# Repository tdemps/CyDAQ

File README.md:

# master_EE_224
This is the repository for the Iowa State University teaching lab's CyDAQ hardware. The CyDAQ is a data acquisition system designed around the Zybo Z7 FPGA. It features analog inputs to a filter block feature 7 adjustable filters, power breakout, and Zybo PMOD breakouts. 

## Filters:
The board features the following 7 filters:
    - 60 Hz Notch 
    - 1st Order High Pass
    - 1st Order Low Pass
    - 2nd Order Bandpass
    - 6th Order How Pass
    - 6th Order Low pass
    - 6th Order Bandpass

Each of these filters can be selected to process any of the analog inputs, and their outputs are sent to the XADC on the Zybo and the Vout breakout header. 

## Power
The board has three user accessible power rails: 1.8V, 3.3V, and 5.0V. Each rail can source up to 1A. 

## Digital Communication Protocols
The board breaks out I2C and UART busses accessible through the Zybo.

## Firmware
See README in /src/firmware details

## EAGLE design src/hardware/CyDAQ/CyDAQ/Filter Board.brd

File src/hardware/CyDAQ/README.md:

# CyDAQ 2.0

Build of CyDAQ 2.0 with ZYBO Z7

TODO:

Design power block and add sheet

Import filter design

Establish I/O connectors

Design ADC front end

Design filter board input mux

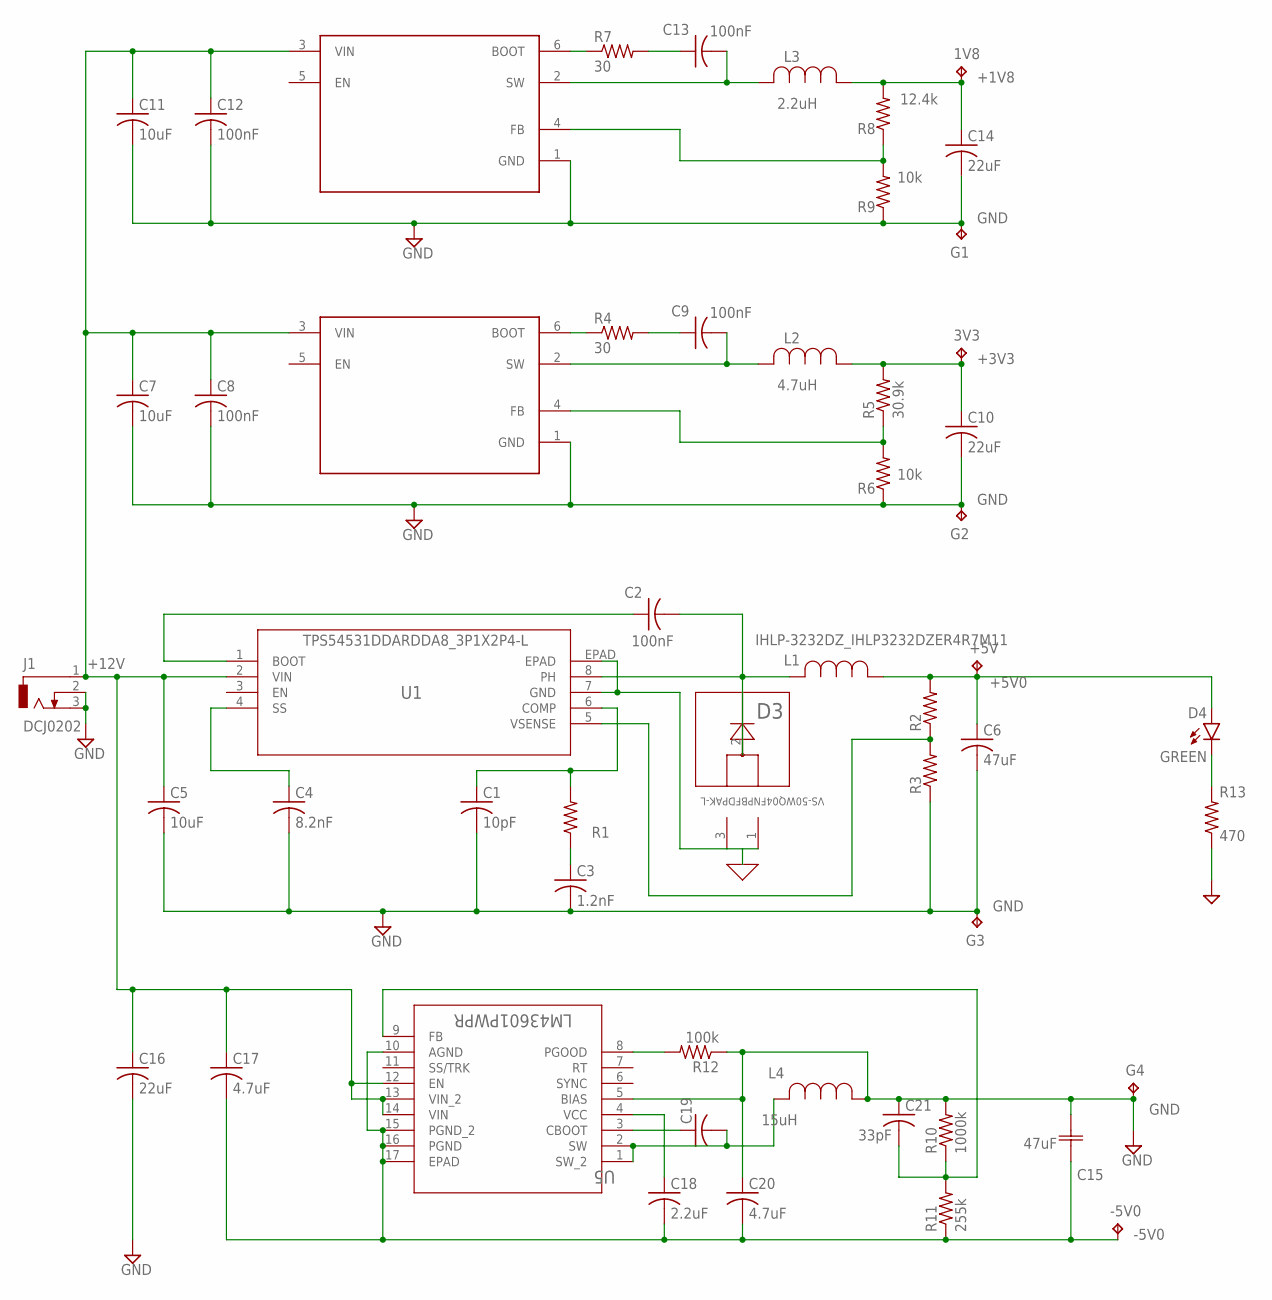
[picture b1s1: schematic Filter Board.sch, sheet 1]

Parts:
1V8, 3V3: TPPAD1-13; P1-13
+5V: TPPAD1-13; P1-13
-5V0: TPPAD1-13; P1-13
C1: 10pF; C0805
C2, C8, C9, C12, C13: 100nF; C0805
C3: 1.2nF; C0805
C4: 8.2nF; C1206
C5: 10uF; C1210
C6: 47uF; C1210
C7, C11: 10uF; C0805
C10, C14: 22uF; C0805
C15: 47uF; CGA9N3X7R1_CAP_5750
C16: 22uF; C1210
C17, C20: 4.7uF; C0805
C18: 2.2uF; C0805
C19: C-USC0805; C0805
C21: 33pF; C0805
D3: VS-50WQ04FNPBFDPAK-L; DPAK-L
D4: GREEN; LED-1206
G1, G2, G3, G4: TPPAD1-13; P1-13
J1: DCJ0202
L1: IHLP-3232DZ_IHLP3232DZER4R7M11; IHLP-3232DZ_IND_IHLP-3232DZ
L2: 4.7uH; IND_5022
L3: 2.2uH; IND_NLCV32TR; MANUFACTURER_PART_NUMBER NLCV32T-2R2M-PFR
L4: 15uH; IFSC-1515A_IND_IFSC_1515AH
R1, R2, R3: R-US_R0805; R0805
R4, R7: 30; R0805
R5: 30.9k; R0805
R6, R9: 10k; R0805
R8: 12.4k; R0805
R10: 1000k; R0805
R11: 255k; R0805
R12: 100k; R0805
R13: 470; R0805
U1: TPS54531DDARDDA8_3P1X2P4-L; DDA8_3P1X2P4-L
U3, U4: TPS56339; TSOT23-6_DDC
U5: LM43601PWPR; PWP16

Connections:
+1V8: 1V8.TP, C14.1, L3.1, R8.2; also elsewhere on the board
+3V3: 3V3.TP, C10.1, L2.1, R5.2; also elsewhere on the board
+5V0: +5V.TP, C6.1, D4.A, L1.1, R2.2; also elsewhere on the board
+12V: C5.1, C7.1, C8.1, C11.1, C12.1, C16.1, C17.1, J1.1, U1.2 (VIN), U3.3 (VIN), U4.3 (VIN), U5.12 (EN), U5.13 (VIN_2), U5.14 (VIN); also elsewhere on the board
-5V0: -5V0.TP, C15.2, C17.2, C18.2, C20.2, R11.1, U5.10 (AGND), U5.15 (PGND_2), U5.16 (PGND), U5.17 (EPAD); also elsewhere on the board
BOOT: C19.1, U5.3 (CBOOT)
FB: C21.2, R10.1, R11.2, U5.9 (FB)
GND: C1.2, C3.2, C4.2, C5.2, C6.2, C7.2, C8.2, C10.2, C11.2, C12.2, C14.2, C15.1, C16.2, C20.1, C21.1, D3.1, D3.3, G1.TP, G2.TP, G3.TP, G4.TP, J1.2, J1.3, L4.1, R3.1, R6.1, R9.1, R10.2, R12.1, R13.1, U1.7 (GND), U1.EPAD, U3.1 (GND), U4.1 (GND), U5.5 (BIAS); also elsewhere on the board
unnamed: C3.1, R1.1
unnamed: R2.1, R3.2, U1.5 (VSENSE)
unnamed: C2.1, U1.1 (BOOT)
unnamed: C2.2, D3.2, L1.2, U1.8 (PH)
unnamed: C4.1, U1.4 (SS)
unnamed: C1.1, R1.2, U1.6 (COMP)
unnamed: R4.1, U3.6 (BOOT)
unnamed: C9.1, R4.2
unnamed: C9.2, L2.2, U3.2 (SW)
unnamed: R7.1, U4.6 (BOOT)
unnamed: R5.1, R6.2, U3.4 (FB)
unnamed: C13.1, R7.2
unnamed: C13.2, L3.2, U4.2 (SW)
unnamed: R8.1, R9.2, U4.4 (FB)
unnamed: C18.1, U5.4 (VCC)
unnamed: D4.C, R13.2
PGOOD: R12.2, U5.8 (PGOOD)
SW: C19.2, L4.2, U5.1 (SW_2), U5.2 (SW)

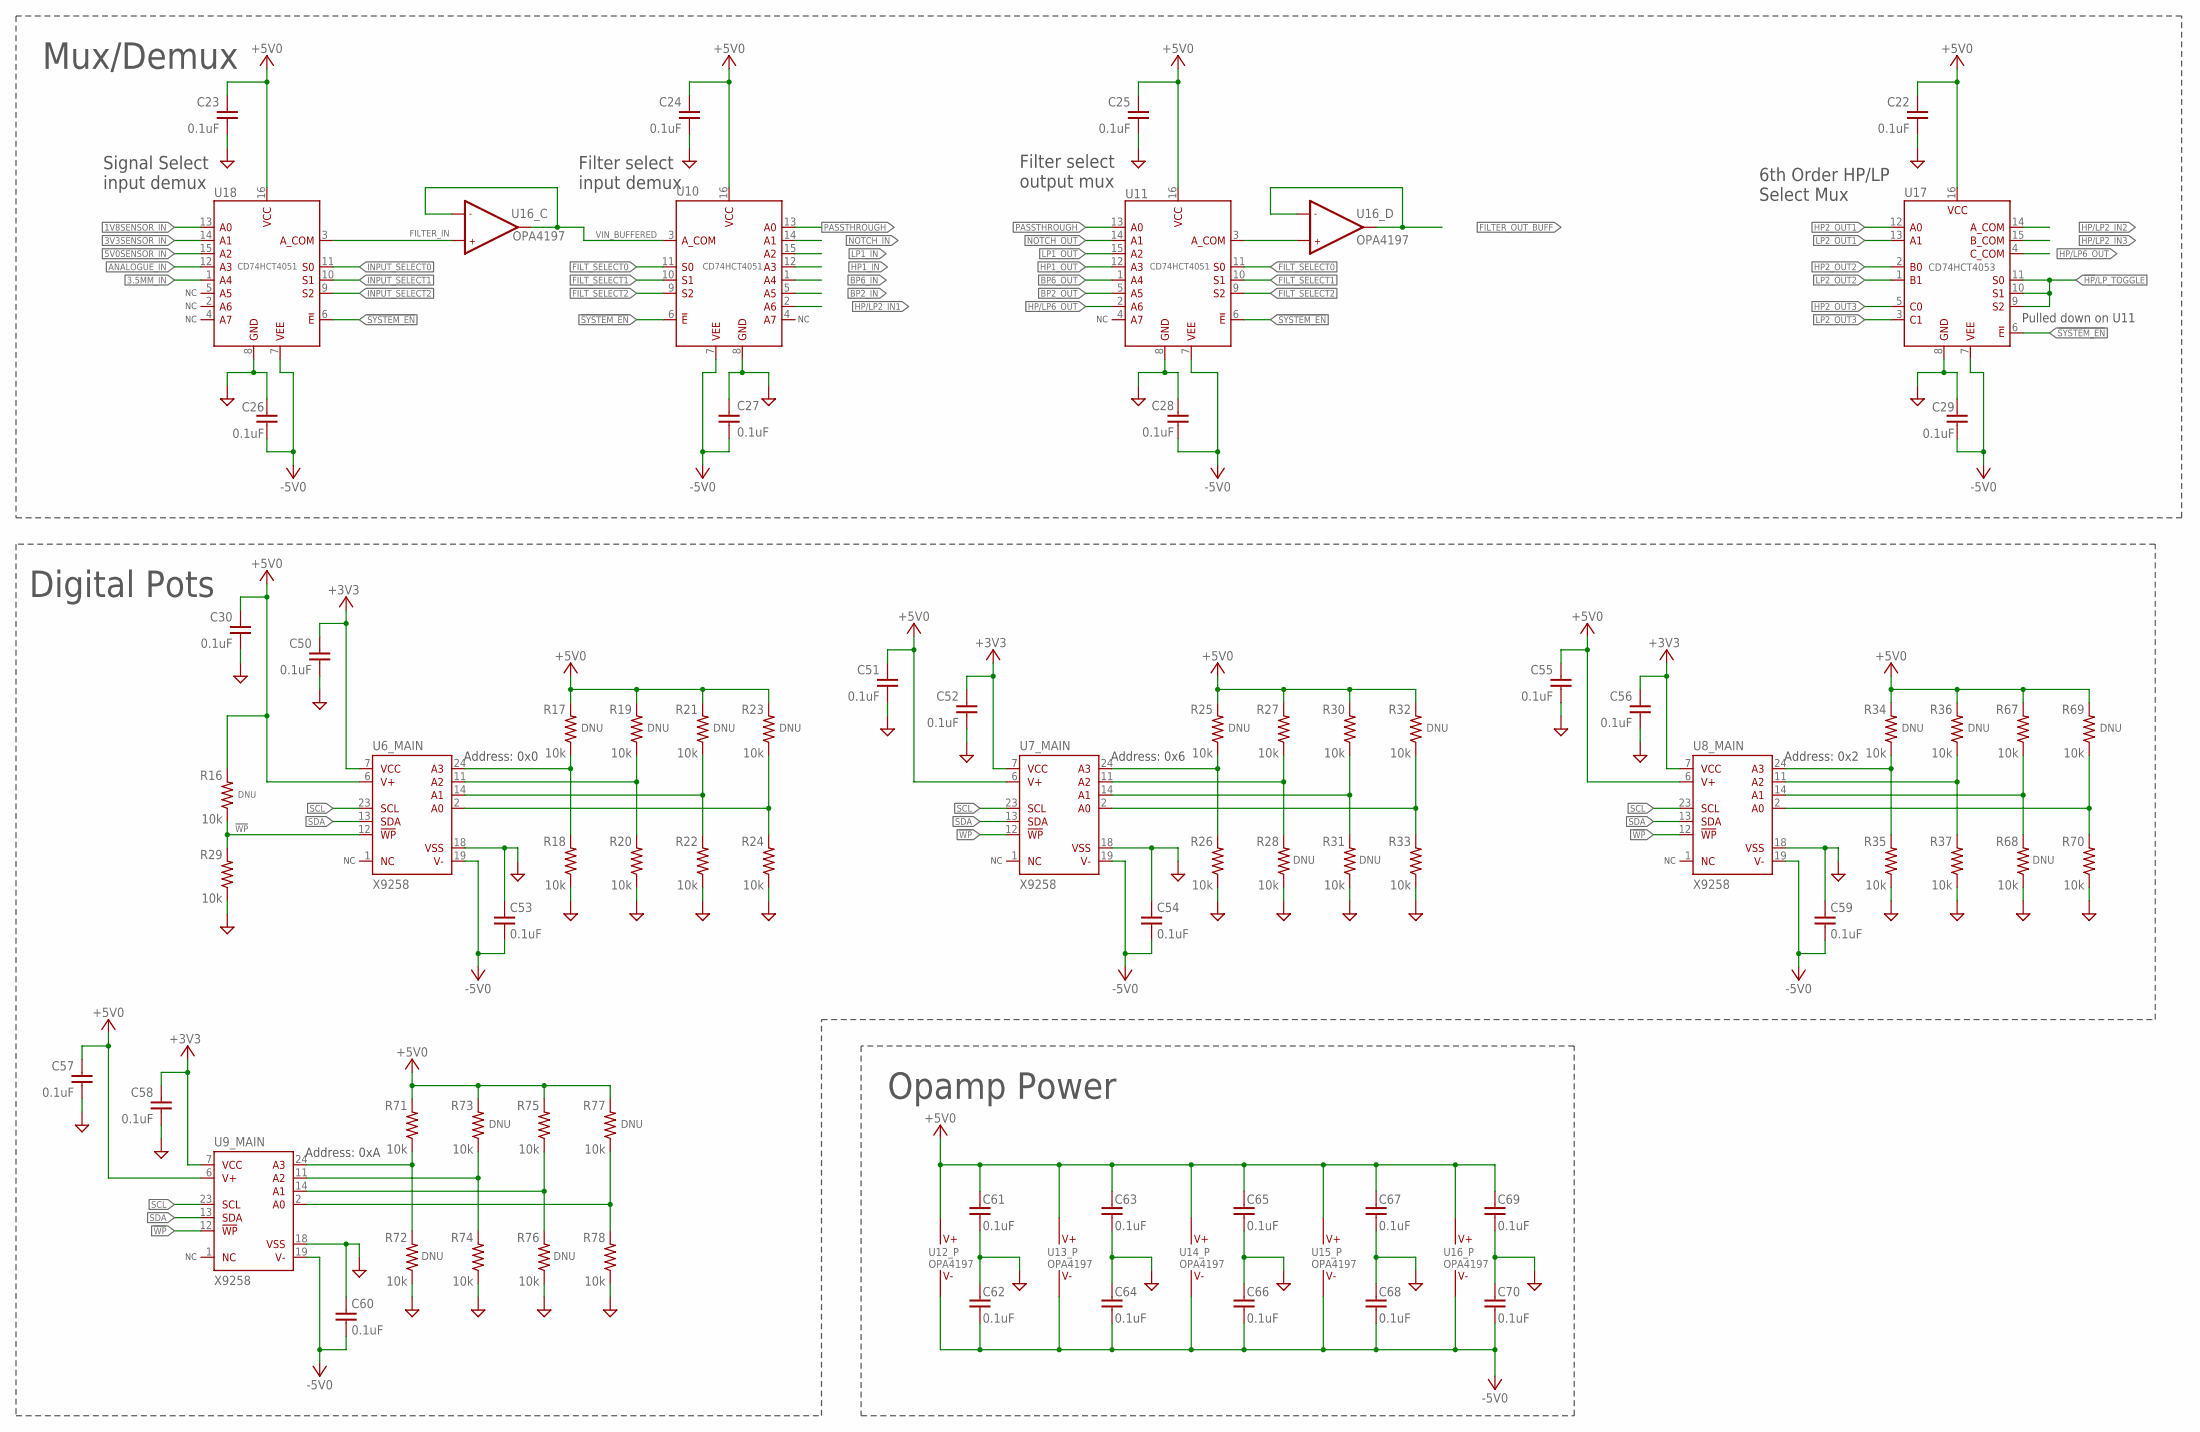
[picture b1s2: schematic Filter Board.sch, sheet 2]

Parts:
C22, C23, C24, C25, C26, C27, C28, C29, C30, C50, C51, C52, C53, C54, C55, C56, C57, C58, C59, C60, C61, C62, C63, C64, C65, C66, C67, C68, C69, C70: 0.1uF; 0805_H0.75
R16, R17, R18, R19, R20, R21, R22, R23, R24, R25, R26, R27, R28, R29, R30, R31, R32, R33, R34, R35, R36, R37, R67, R68, R69, R70, R71, R72, R73, R74, R75, R76, R77, R78: 10k; 0805
U6, U7, U8, U9: X9258; SOIC127P1030X250-25T200X300
U10, U11, U18: CD74HCT4051; SOIC127P600X144-16
U12, U13, U14, U15, U16: OPA4197; SOIC127P600X144-14
U17: CD74HCT4053; SOIC127P600X144-16

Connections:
1V8SENSOR_IN: U18.13 (A0); also elsewhere on the board
3.5MM_IN: U18.1 (A4); also elsewhere on the board
3V3SENSOR_IN: U18.14 (A1); also elsewhere on the board
5V0SENSOR_IN: U18.15 (A2); also elsewhere on the board
!HP!/LP_TOGGLE: U17.9 (S2), U17.10 (S1), U17.11 (S0); also elsewhere on the board
!SYSTEM_EN: U10.6 (!E), U11.6 (!E), U17.6 (!E), U18.6 (!E); also elsewhere on the board
!WP: R16.1, R29.2, U6.12 (!WP), U7.12 (!WP), U8.12 (!WP), U9.12 (!WP)
+3V3: C50.1, C52.1, C56.1, C58.1, U6.7 (VCC), U7.7 (VCC), U8.7 (VCC), U9.7 (VCC); also elsewhere on the board
+5V0: C22.1, C23.1, C24.1, C25.1, C30.1, C51.1, C55.1, C57.1, C61.1, C63.1, C65.1, C67.1, C69.1, R16.2, R17.2, R19.2, R21.2, R23.2, R25.2, R27.2, R30.2, R32.2, R34.2, R36.2, R67.2, R69.2, R71.2, R73.2, R75.2, R77.2, U6.6 (V+), U7.6 (V+), U8.6 (V+), U9.6 (V+), U10.16 (VCC), U11.16 (VCC), U12.4 (V+), U13.4 (V+), U14.4 (V+), U15.4 (V+), U16.4 (V+), U17.16 (VCC), U18.16 (VCC); also elsewhere on the board
-5V0: C26.2, C27.1, C28.2, C29.2, C53.2, C54.2, C59.2, C60.2, C62.2, C64.2, C66.2, C68.2, C70.2, U6.19 (V-), U7.19 (V-), U8.19 (V-), U9.19 (V-), U10.7 (VEE), U11.7 (VEE), U12.11 (V-), U13.11 (V-), U14.11 (V-), U15.11 (V-), U16.11 (V-), U17.7 (VEE), U18.7 (VEE); also elsewhere on the board
ANALOGUE_IN: U18.12 (A3); also elsewhere on the board
BP2_IN: U10.5 (A5); also elsewhere on the board
BP2_OUT: U11.5 (A5); also elsewhere on the board
BP6_IN: U10.1 (A4); also elsewhere on the board
BP6_OUT: U11.1 (A4); also elsewhere on the board
FILTER_IN: U16.10 (+IN), U18.3 (A_COM)
FILTER_OUT_BUFF: U16.13 (-IN), U16.14 (OUT); also elsewhere on the board
FILT_SELECT0: U10.11 (S0), U11.11 (S0); also elsewhere on the board
FILT_SELECT1: U10.10 (S1), U11.10 (S1); also elsewhere on the board
FILT_SELECT2: U10.9 (S2), U11.9 (S2); also elsewhere on the board
GND: C22.2, C23.2, C24.2, C25.2, C26.1, C27.2, C28.1, C29.1, C30.2, C50.2, C51.2, C52.2, C53.1, C54.1, C55.2, C56.2, C57.2, C58.2, C59.1, C60.1, C61.2, C62.1, C63.2, C64.1, C65.2, C66.1, C67.2, C68.1, C69.2, C70.1, R18.1, R20.1, R22.1, R24.1, R26.1, R28.1, R29.1, R31.1, R33.1, R35.1, R37.1, R68.1, R70.1, R72.1, R74.1, R76.1, R78.1, U6.18 (VSS), U7.18 (VSS), U8.18 (VSS), U9.18 (VSS), U10.8 (GND), U11.8 (GND), U17.8 (GND), U18.8 (GND); also elsewhere on the board
HP1_IN: U10.12 (A3); also elsewhere on the board
HP1_OUT: U11.12 (A3); also elsewhere on the board
HP2_OUT1: U17.12 (A0); also elsewhere on the board
HP2_OUT2: U17.2 (B0); also elsewhere on the board
HP2_OUT3: U17.5 (C0); also elsewhere on the board
HP/LP2_IN1: U10.2 (A6); also elsewhere on the board
HP/LP2_IN2: U17.14 (A_COM); also elsewhere on the board
HP/LP2_IN3: U17.15 (B_COM); also elsewhere on the board
HP/LP6_OUT: U11.2 (A6), U17.4 (C_COM)
INPUT_SELECT0: U18.11 (S0); also elsewhere on the board
INPUT_SELECT1: U18.10 (S1); also elsewhere on the board
INPUT_SELECT2: U18.9 (S2); also elsewhere on the board
LP1_IN: U10.15 (A2); also elsewhere on the board
LP1_OUT: U11.15 (A2); also elsewhere on the board
LP2_OUT1: U17.13 (A1); also elsewhere on the board
LP2_OUT2: U17.1 (B1); also elsewhere on the board
LP2_OUT3: U17.3 (C1); also elsewhere on the board
unnamed: R17.1, R18.2, U6.24 (A3)
unnamed: R19.1, R20.2, U6.11 (A2)
unnamed: R21.1, R22.2, U6.14 (A1)
unnamed: U11.3 (A_COM), U16.12 (+IN)
unnamed: R23.1, R24.2, U6.2 (A0)
unnamed: R25.1, R26.2, U7.24 (A3)
unnamed: R27.1, R28.2, U7.11 (A2)
unnamed: R30.1, R31.2, U7.14 (A1)
unnamed: R32.1, R33.2, U7.2 (A0)
unnamed: R34.1, R35.2, U8.24 (A3)
unnamed: R36.1, R37.2, U8.11 (A2)
unnamed: R67.1, R68.2, U8.14 (A1)
unnamed: R69.1, R70.2, U8.2 (A0)
unnamed: R71.1, R72.2, U9.24 (A3)
unnamed: R73.1, R74.2, U9.11 (A2)
unnamed: R75.1, R76.2, U9.14 (A1)
unnamed: R77.1, R78.2, U9.2 (A0)
NOTCH_IN: U10.14 (A1); also elsewhere on the board
NOTCH_OUT: U11.14 (A1); also elsewhere on the board
PASSTHROUGH: U10.13 (A0), U11.13 (A0)
SCL: U6.23 (SCL), U7.23 (SCL), U8.23 (SCL), U9.23 (SCL); also elsewhere on the board
SDA: U6.13 (SDA), U7.13 (SDA), U8.13 (SDA), U9.13 (SDA); also elsewhere on the board
VIN_BUFFERED: U10.3 (A_COM), U16.8 (OUT), U16.9 (-IN)

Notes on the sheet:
Address: 0x0
Address: 0x6
Address: 0x2
Address: 0xA
Opamp Power
Digital Pots
Mux/Demux
6th Order HP/LP Select Mux
Filter select input demux
Filter select output mux
Pulled down on U11
Signal Select input demux

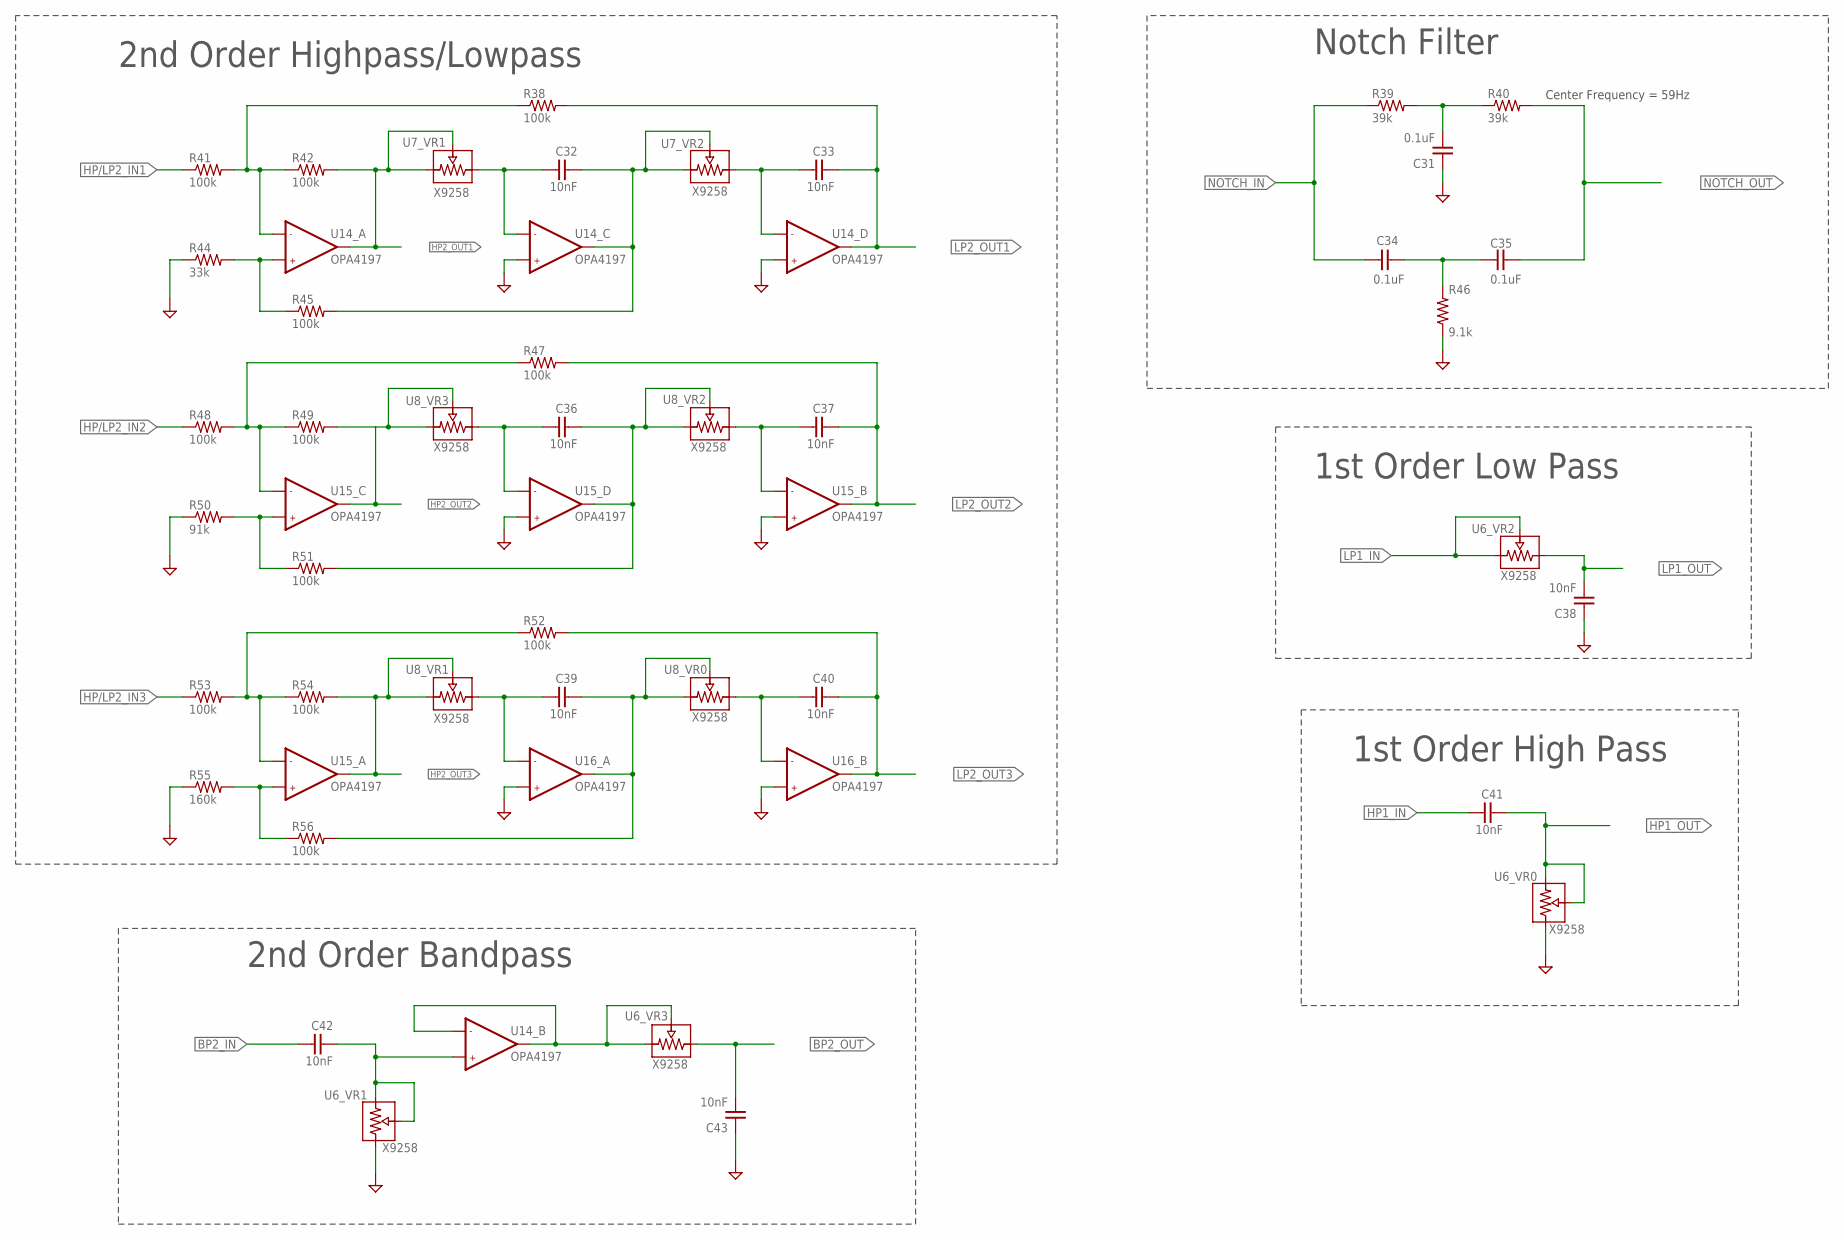
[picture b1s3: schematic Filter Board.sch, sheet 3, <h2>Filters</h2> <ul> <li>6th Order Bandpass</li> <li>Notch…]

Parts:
C31, C34, C35: 0.1uF; 0805_H0.75
C32, C33, C36, C37, C38, C39, C40, C41, C42, C43: 10nF; 0805_H0.75
R38, R41, R42, R45, R47, R48, R49, R51, R52, R53, R54, R56: 100k; 0805
R39, R40: 39k; 0805
R44: 33k; 0805
R46: 9.1k; 0805
R50: 91k; 0805
R55: 160k; 0805
U6, U7, U8: X9258; SOIC127P1030X250-25T200X300
U14, U15, U16: OPA4197; SOIC127P600X144-14

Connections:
BP2_IN: C42.1; also elsewhere on the board
BP2_OUT: C43.2, U6.5 (L); also elsewhere on the board
GND: C31.1, C38.1, C43.1, R44.1, R46.1, R50.1, R55.1, U6.8 (L), U6.15 (L), U14.10 (+IN), U14.12 (+IN), U15.5 (+IN), U15.12 (+IN), U16.3 (+IN), U16.5 (+IN); also elsewhere on the board
HP1_IN: C41.1; also elsewhere on the board
HP1_OUT: C41.2, U6.9 (H), U6.10 (W); also elsewhere on the board
HP2_OUT1: R42.2, U7.16 (H), U7.17 (W), U14.1 (OUT); also elsewhere on the board
HP2_OUT2: R49.2, U8.3 (W), U8.4 (H), U15.8 (OUT); also elsewhere on the board
HP2_OUT3: R54.2, U8.16 (H), U8.17 (W), U15.1 (OUT); also elsewhere on the board
HP/LP2_IN1: R41.1; also elsewhere on the board
HP/LP2_IN2: R48.1; also elsewhere on the board
HP/LP2_IN3: R53.1; also elsewhere on the board
LP1_IN: U6.20 (W), U6.21 (H); also elsewhere on the board
LP1_OUT: C38.2, U6.22 (L); also elsewhere on the board
LP2_OUT1: C33.2, R38.2, U14.14 (OUT); also elsewhere on the board
LP2_OUT2: C37.2, R47.2, U15.7 (OUT); also elsewhere on the board
LP2_OUT3: C40.2, R52.2, U16.7 (OUT); also elsewhere on the board
unnamed: C31.2, R39.2, R40.1
unnamed: C34.2, C35.1, R46.2
unnamed: C42.2, U6.16 (H), U6.17 (W), U14.5 (+IN)
unnamed: U6.3 (W), U6.4 (H), U14.6 (-IN), U14.7 (OUT)
unnamed: R44.2, R45.1, U14.3 (+IN)
unnamed: R38.1, R41.2, R42.1, U14.2 (-IN)
unnamed: C32.1, U7.15 (L), U14.9 (-IN)
unnamed: C32.2, R45.2, U7.20 (W), U7.21 (H), U14.8 (OUT)
unnamed: C33.1, U7.22 (L), U14.13 (-IN)
unnamed: R50.2, R51.1, U15.10 (+IN)
unnamed: R47.1, R48.2, R49.1, U15.9 (-IN)
unnamed: C36.1, U8.5 (L), U15.13 (-IN)
unnamed: C36.2, R51.2, U8.20 (W), U8.21 (H), U15.14 (OUT)
unnamed: C37.1, U8.22 (L), U15.6 (-IN)
unnamed: R55.2, R56.1, U15.3 (+IN)
unnamed: R52.1, R53.2, R54.1, U15.2 (-IN)
unnamed: C39.1, U8.15 (L), U16.2 (-IN)
unnamed: C39.2, R56.2, U8.9 (H), U8.10 (W), U16.1 (OUT)
unnamed: C40.1, U8.8 (L), U16.6 (-IN)
NOTCH_IN: C34.1, R39.1; also elsewhere on the board
NOTCH_OUT: C35.2, R40.2; also elsewhere on the board

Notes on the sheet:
Center Frequency = 59Hz
Notch Filter
1st Order High Pass
1st Order Low Pass
2nd Order Bandpass
2nd Order Highpass/Lowpass

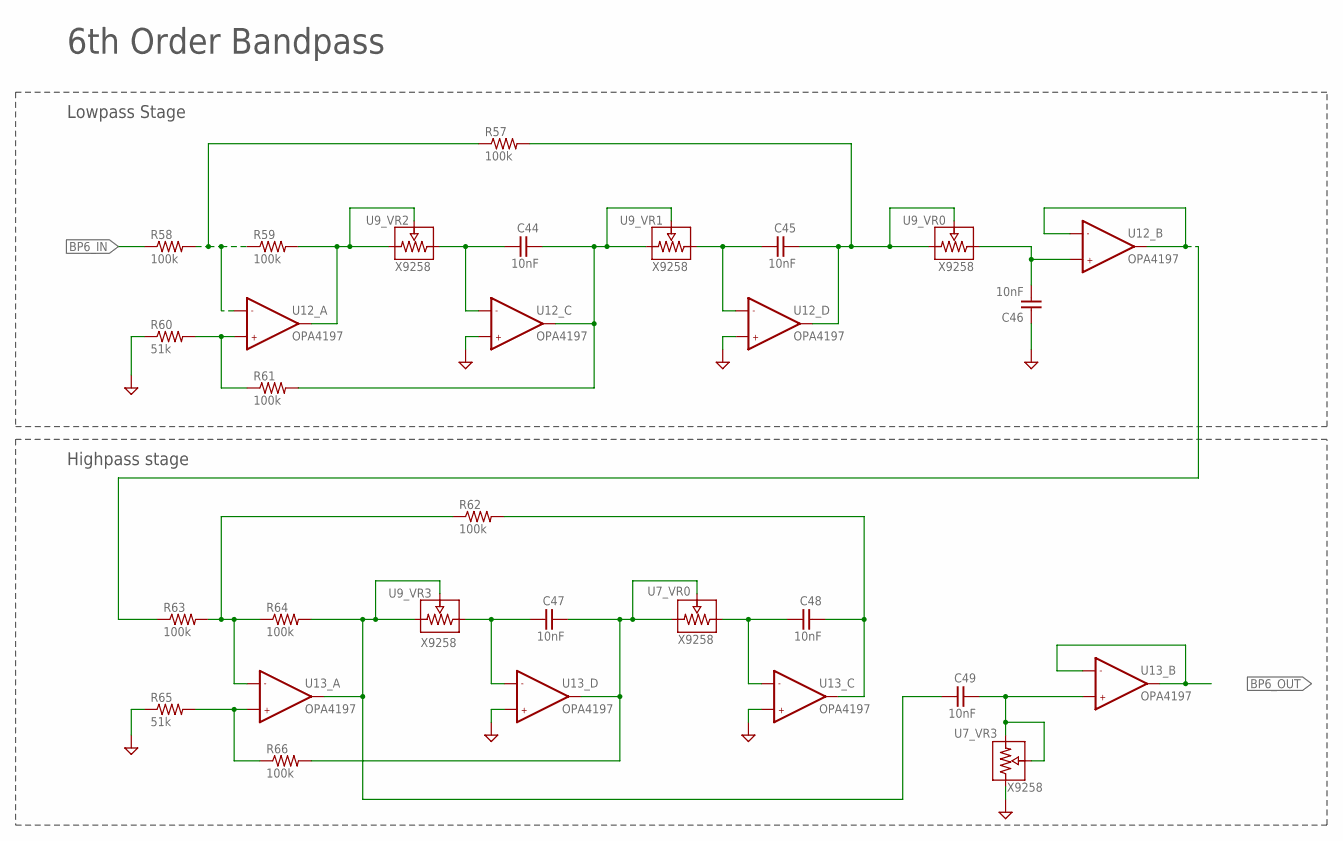
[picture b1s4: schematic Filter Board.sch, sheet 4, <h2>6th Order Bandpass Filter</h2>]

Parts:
C44, C45, C46, C47, C48, C49: 10nF; 0805_H0.75
R57, R58, R59, R61, R62, R63, R64, R66: 100k; 0805
R60, R65: 51k; 0805
U7, U9: X9258; SOIC127P1030X250-25T200X300
U12, U13: OPA4197; SOIC127P600X144-14

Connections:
BP6_HPOUT: C44.2, R61.2, U9.16 (H), U9.17 (W), U12.8 (OUT)
BP6_IN: R58.1; also elsewhere on the board
BP6_OUT: U13.6 (-IN), U13.7 (OUT); also elsewhere on the board
GND: C46.1, R60.1, R65.1, U7.5 (L), U12.10 (+IN), U12.12 (+IN), U13.10 (+IN), U13.12 (+IN); also elsewhere on the board
unnamed: R57.1, R58.2, R59.1, U12.2 (-IN)
unnamed: R60.2, R61.1, U12.3 (+IN)
unnamed: R59.2, U9.20 (W), U9.21 (H), U12.1 (OUT)
unnamed: C44.1, U9.22 (L), U12.9 (-IN)
unnamed: C45.1, U9.15 (L), U12.13 (-IN)
unnamed: C45.2, R57.2, U9.9 (H), U9.10 (W), U12.14 (OUT)
unnamed: C46.2, U9.8 (L), U12.5 (+IN)
unnamed: R63.1, U12.6 (-IN), U12.7 (OUT)
unnamed: R62.1, R63.2, R64.1, U13.2 (-IN)
unnamed: R65.2, R66.1, U13.3 (+IN)
unnamed: C49.1, R64.2, U9.3 (W), U9.4 (H), U13.1 (OUT)
unnamed: C47.1, U9.5 (L), U13.13 (-IN)
unnamed: C47.2, R66.2, U7.9 (H), U7.10 (W), U13.14 (OUT)
unnamed: C48.1, U7.8 (L), U13.9 (-IN)
unnamed: C48.2, R62.2, U13.8 (OUT)
unnamed: C49.2, U7.3 (W), U7.4 (H), U13.5 (+IN)

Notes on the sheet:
Lowpass Stage
Highpass stage
6th Order Bandpass

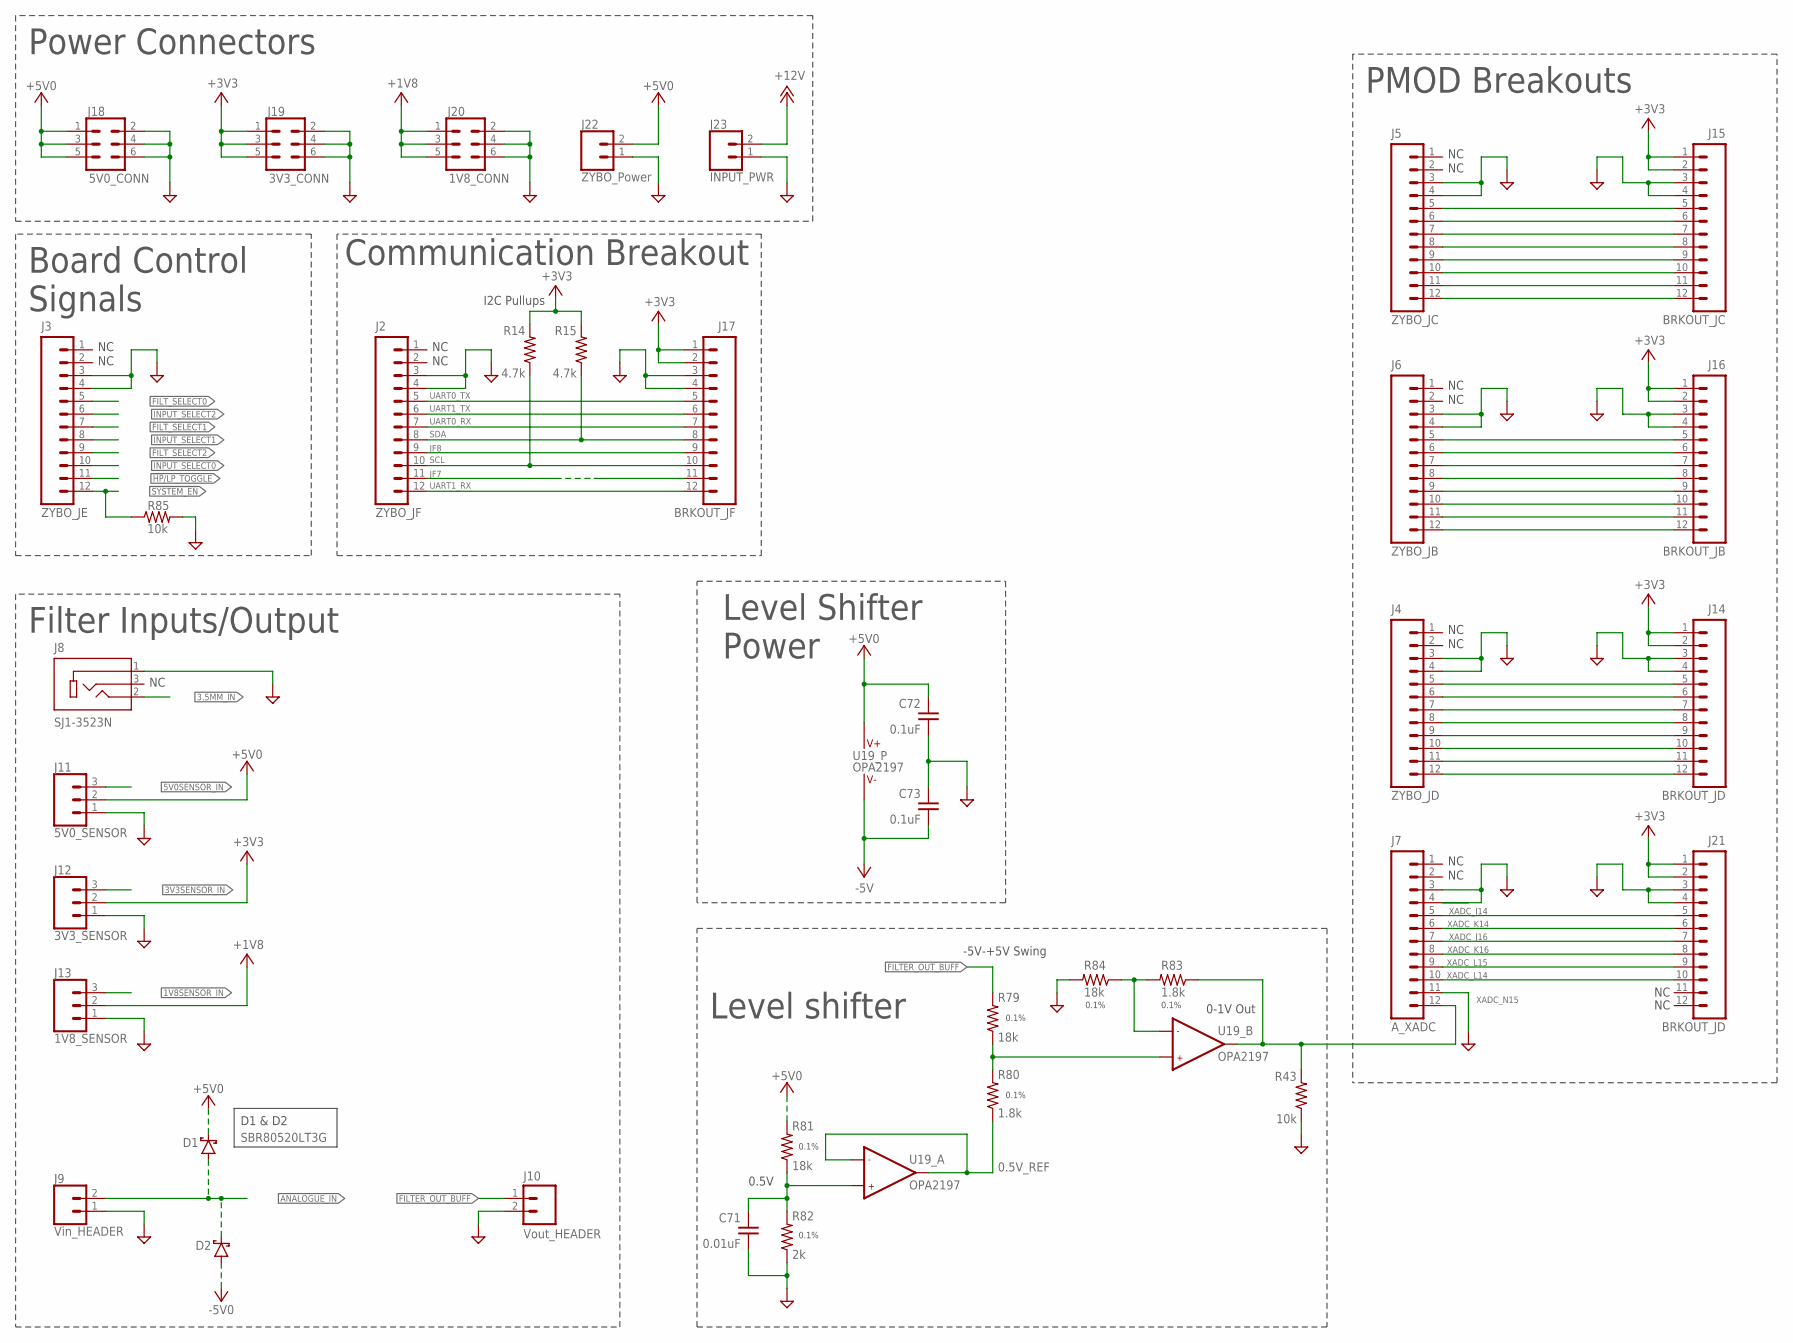
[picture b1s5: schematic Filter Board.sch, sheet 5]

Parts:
C71: 0.01uF; 0805_H0.75
C72, C73: 0.1uF; 0805_H0.75
D1, D2: SBR80520LT3G; SOD123
J2: ZYBO_JF; FEMALE_HEADER-2X6
J3: ZYBO_JE; FEMALE_HEADER-2X6
J4: ZYBO_JD; FEMALE_HEADER-2X6
J5: ZYBO_JC; FEMALE_HEADER-2X6
J6: ZYBO_JB; FEMALE_HEADER-2X6
J7: A_XADC; FEMALE_HEADER-2X6
J8: SJ1-3523N; CUI_SJ1-3523N
J9: Vin_HEADER; 1X02_LOCK
J10: Vout_HEADER; 1X02_LOCK
J11: 5V0_SENSOR; 1X03_LOCK
J12: 3V3_SENSOR; 1X03_LOCK
J13: 1V8_SENSOR; 1X03_LOCK
J14, J21: BRKOUT_JD; FEMALE_HEADER-2X6
J15: BRKOUT_JC; FEMALE_HEADER-2X6
J16: BRKOUT_JB; FEMALE_HEADER-2X6
J17: BRKOUT_JF; FEMALE_HEADER-2X6
J18: 5V0_CONN; 2X3
J19: 3V3_CONN; 2X3
J20: 1V8_CONN; 2X3
J22: ZYBO_Power; 1X02_LOCK
J23: INPUT_PWR; 1X02_LOCK
R14, R15: 4.7k; 0805
R43, R85: 10k; 0805
R79, R81, R84: 18k; 0805
R80, R83: 1.8k; 0805
R82: 2k; 0805
U19: OPA2197; SO08

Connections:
0.5V_REF: R80.1, U19.1 (OUT), U19.2 (-IN)
1V8SENSOR_IN: J13.3; also elsewhere on the board
3.5MM_IN: J8.2; also elsewhere on the board
3V3SENSOR_IN: J12.3; also elsewhere on the board
5V0SENSOR_IN: J11.3; also elsewhere on the board
!HP!/LP_TOGGLE: J3.11; also elsewhere on the board
!SYSTEM_EN: J3.12, R85.1; also elsewhere on the board
+1V8: J13.2, J20.1, J20.3, J20.5; also elsewhere on the board
+3V3: J12.2, J14.1, J14.2, J15.1, J15.2, J16.1, J16.2, J17.1, J17.2, J19.1, J19.3, J19.5, J21.1, J21.2, R14.2, R15.2; also elsewhere on the board
+5V0: C72.1, D1.1 (C), J11.2, J18.1, J18.3, J18.5, J22.2, R81.2, U19.8 (V+); also elsewhere on the board
+12V: J23.2; also elsewhere on the board
-5V0: C73.2, D2.2 (A), U19.4 (V-); also elsewhere on the board
ANALOGUE_IN: D1.2 (A), D2.1 (C), J9.2; also elsewhere on the board
FILTER_OUT_BUFF: J10.1, R79.2; also elsewhere on the board
FILT_SELECT0: J3.5; also elsewhere on the board
FILT_SELECT1: J3.7; also elsewhere on the board
FILT_SELECT2: J3.9; also elsewhere on the board
GND: C71.2, C72.2, C73.1, J2.3, J2.4, J3.3, J3.4, J4.3, J4.4, J5.3, J5.4, J6.3, J6.4, J7.3, J7.4, J7.11, J8.1, J9.1, J10.2, J11.1, J12.1, J13.1, J14.3, J14.4, J15.3, J15.4, J16.3, J16.4, J17.3, J17.4, J18.2, J18.4, J18.6, J19.2, J19.4, J19.6, J20.2, J20.4, J20.6, J21.3, J21.4, J22.1, J23.1, R43.1, R82.1, R84.2, R85.2; also elsewhere on the board
INPUT_SELECT0: J3.10; also elsewhere on the board
INPUT_SELECT1: J3.8; also elsewhere on the board
INPUT_SELECT2: J3.6; also elsewhere on the board
JB1: J6.12, J16.12
JB2: J6.10, J16.10
JB3: J6.8, J16.8
JB4: J6.6, J16.6
JB7: J6.11, J16.11
JB8: J6.9, J16.9
JB9: J6.7, J16.7
JB10: J6.5, J16.5
JC1: J5.12, J15.12
JC2: J5.10, J15.10
JC3: J5.8, J15.8
JC4: J5.6, J15.6
JC7: J5.11, J15.11
JC8: J5.9, J15.9
JC9: J5.7, J15.7
JC10: J5.5, J15.5
JD1: J4.12, J14.12
JD2: J4.10, J14.10
JD3: J4.8, J14.8
JD4: J4.6, J14.6
JD7\: J4.11, J14.11
JD8: J4.9, J14.9
JD9: J4.7, J14.7
JD10: J4.5, J14.5
JF7: J2.11, J17.11
JF8: J2.9, J17.9
unnamed: J7.12, R43.2, R83.1, U19.7 (OUT)
unnamed: R83.2, R84.1, U19.6 (-IN)
SCL: J2.10, J17.10, R14.1; also elsewhere on the board
SDA: J2.8, J17.8, R15.1; also elsewhere on the board
UART0_RX: J2.7, J17.7
UART0_TX: J2.5, J17.5
UART1_RX: J2.12, J17.12
UART1_TX: J2.6, J17.6
XADC_J14: J7.5, J21.5
XADC_J16: J7.7, J21.7
XADC_K14: J7.6, J21.6
XADC_K16: J7.8, J21.8
XADC_L14: J7.10, J21.10
XADC_L15: J7.9, J21.9
XADC_N1: C71.1, R81.1, R82.2, U19.3 (+IN)
XADC_N15: R79.1, R80.2, U19.5 (+IN)

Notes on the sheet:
D1 & D2
0.5V
0-1V Out
-5V-+5V Swing
0.1%
Level shifter
Level Shifter Power
Power Connectors
PMOD Breakouts
Communication Breakout
Board Control Signals
Filter Inputs/Output
I2C Pullups

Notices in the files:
parts and their libraries:
SparkFun-Connectors: Licensing: Creative Commons ShareAlike 4.0 International - https://creativecommons.org/licenses/by-sa/4.0
